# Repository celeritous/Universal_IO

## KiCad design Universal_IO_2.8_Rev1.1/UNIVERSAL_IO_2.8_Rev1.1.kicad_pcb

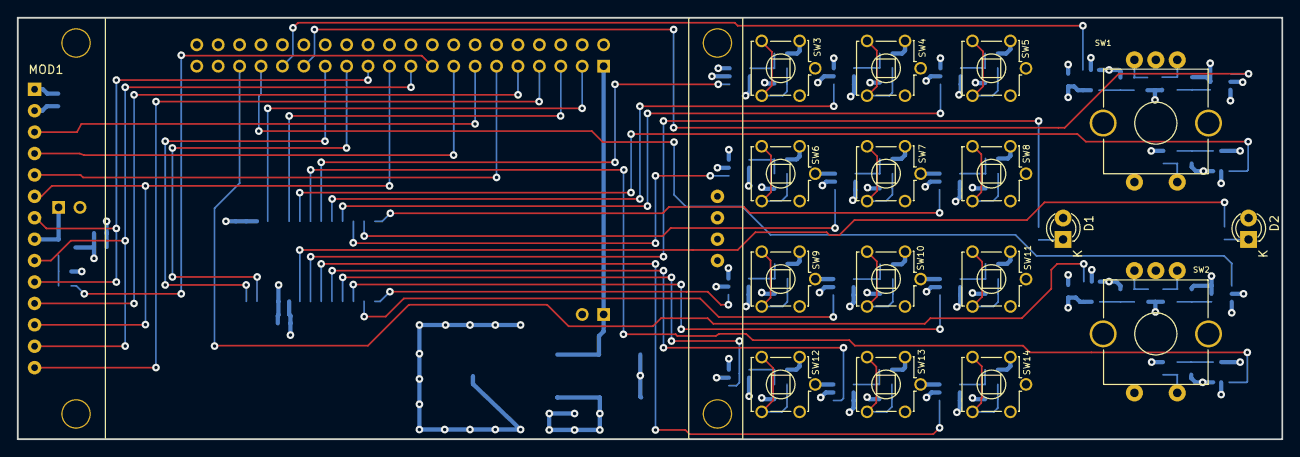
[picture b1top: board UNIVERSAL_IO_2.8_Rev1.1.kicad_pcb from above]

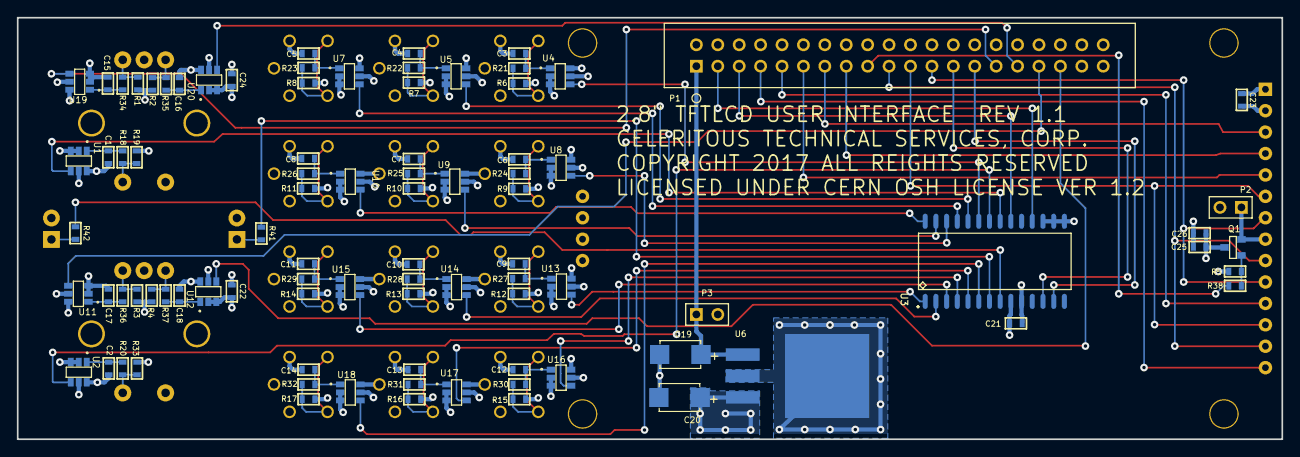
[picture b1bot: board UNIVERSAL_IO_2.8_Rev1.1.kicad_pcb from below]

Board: 4 copper layers, 150.0 x 50.0 mm, 107 parts (90 on the bottom side), 76 nets.

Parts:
C1, C2, C3, C4, C5, C6, C7, C8, C9, C10, C11, C12, C13, C14, C15, C16, C17, C18, C21, C22, C23, C24, C25: 0.10uF; P0603
C19, C20: 47uF; CAPACITOR_TANTALUM_C
C26: 10.0uF; P0603
D1, D2: Led_Small; LED_3MM_TH
MOD1: TFT_320X240_2.4_SPI; TFT_320x260_2.8_SPI
P1: Header_2x20; Header_2x20_Shrouded_100mil
P2, P3: Header_2x1; Header_2x1_Shrouded_100mil
Q1: CMPDM302PH; SOT23-3
R1, R2, R3, R4, R5, R6, R7, R8, R9, R10, R11, R12, R13, R14, R15, R16, R17, R19, R33: 10.0kΩ; P0603
R18, R20, R21, R22, R23, R24, R25, R26, R27, R28, R29, R30, R31, R32, R34, R35, R36, R37: 1.00kΩ; P0603
R38, R41, R42: 470.0Ω; P0603
SW1, SW2: ENCODER_W/PB; SW_PEC11_QUAD_ENCODER_TH_PB
SW3, SW4, SW5, SW6, SW7, SW8, SW9, SW10, SW11, SW12, SW13, SW14: PUSHBUTTON_SPST_6MM_TH_GND; SWITCH_PB_6MM_TH_GND
U1, U2, U4, U5, U7, U8, U9, U10, U11, U12, U13, U14, U15, U16, U17, U18, U19, U20: SN74LVC1G97; SOT23-6
U3: MCP23017; SOIC127P1034X267-28
U6: MCP1826S-3302; TO263-3

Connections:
+3.3V: C20.1, C21.1, C22.1, C23.1, C24.1, C25.1, C26.1, D1.A, D2.A, MOD1.1, P2.2, P3.2, Q1.2, R1.1, R2.1, R3.1, R4.1, R5.2, R6.1, R7.1, R8.1, R9.1, R10.1, R11.1, R12.1, R13.1, R14.1, R15.1, R16.1, R17.1, R19.2, R33.2, U1.5, U2.5, U3.9, U4.5, U5.5, U6.3, U7.5, U8.5, U9.5, U10.5, U11.5, U12.5, U13.5, U14.5, U15.5, U16.5, U17.5, U18.5, U19.5, U20.5
+4.3V: C19.1, P1.1, P3.1, U6.1
/DB1: U1.4, U3.21
/DB2: U2.4, U3.22
/DB3: U3.23, U4.4
/DB4: U3.24, U5.4
/DB5: U3.25, U7.4
/DB6: U3.26, U8.4
/DB7: U3.27, U9.4
/DB8: U3.28, U10.4
/DB9: U3.1, U13.4
/DB10: U3.2, U14.4
/DB11: U3.3, U15.4
/DB12: U3.4, U16.4
/DB13: U3.5, U17.4
/DB14: U3.6, U18.4
/DISP_CD: MOD1.5, P1.11
/DISP_CS: MOD1.3, P1.13
/DISP_LED: MOD1.8, P2.1, Q1.3
/DISP_PENIRQ: MOD1.14, P1.7
/DISP_RST: MOD1.4, P1.15
/DISP_TCS: MOD1.11, P1.9
/ENCODER_1A: P1.29, U19.4
/ENCODER_1B: P1.31, U20.4
/ENCODER_2A: P1.33, U11.4
/ENCODER_2B: P1.35, U12.4
/EXP_INT: P1.5, U3.20
/EXP_RST: P1.3, U3.18
/I2C_SCL: P1.25, U3.12
/I2C_SDA: P1.27, U3.13
/LED1: R41.1, U3.7
/LED2: R42.1, U3.8
/PB1: C1.1, R18.2, U1.1
/PB2: C2.1, R20.2, U2.1
/PB3: C3.1, R21.2, U4.1
/PB4: C4.1, R22.2, U5.1
/PB5: C5.1, R23.2, U7.1
/PB6: C6.1, R24.2, U8.1
/PB7: C7.1, R25.2, U9.1
/PB8: C8.1, R26.2, U10.1
/PB9: C9.1, R27.2, U13.1
/PB10: C10.1, R28.2, U14.1
/PB11: C11.1, R29.2, U15.1
/PB12: C12.1, R30.2, U16.1
/PB13: C13.1, R31.2, U17.1
/PB14: C14.1, R32.2, U18.1
/PHA1: R1.2, R34.1, SW1.1
/PHA1D: C15.1, R34.2, U19.1
/PHA2: R3.2, R36.1, SW2.1
/PHA2D: C17.1, R36.2, U11.1
/PHB1: R2.2, R35.1, SW1.3
/PHB1D: C16.1, R35.2, U20.1
/PHB2: R4.2, R37.1, SW2.3
/PHB2D: C18.1, R37.2, U12.1
/PWM: P1.17, R38.1
/SPI_MISO: MOD1.9, MOD1.13, P1.19
/SPI_MOSI: MOD1.6, MOD1.12, P1.21
/SPI_SCK: MOD1.7, MOD1.10, P1.23
/SW3: R6.2, R21.1, SW3.1, SW3.2
/SW4: R7.2, R22.1, SW4.1, SW4.2
/SW5: R8.2, R23.1, SW5.1, SW5.2
/SW6: R9.2, R24.1, SW6.1, SW6.2
/SW7: R10.2, R25.1, SW7.1, SW7.2
/SW8: R11.2, R26.1, SW8.1, SW8.2
/SW9: R12.2, R27.1, SW9.1, SW9.2
/SW10: R13.2, R28.1, SW10.1, SW10.2
/SW11: R14.2, R29.1, SW11.1, SW11.2
/SW12: R15.2, R30.1, SW12.1, SW12.2
/SW13: R16.2, R31.1, SW13.1, SW13.2
/SW14: R17.2, R32.1, SW14.1, SW14.2
GND: C1.2, C2.2, C3.2, C4.2, C5.2, C6.2, C7.2, C8.2, C9.2, C10.2, C11.2, C12.2, C13.2, C14.2, C15.2, C16.2, C17.2, C18.2, C19.2, C20.2, C21.2, C22.2, C23.2, C24.2, C25.2, C26.2, MOD1.2, P1.2, P1.4, P1.6, P1.8, P1.10, P1.12, P1.14, P1.16, P1.18, P1.20, P1.22, P1.24, P1.26, P1.28, P1.30, P1.32, P1.34, P1.36, P1.38, P1.40, SW1.2, SW1.4, SW2.2, SW2.4, SW3.3, SW3.4, SW3.5, SW4.3, SW4.4, SW4.5, SW5.3, SW5.4, SW5.5, SW6.3, SW6.4, SW6.5, SW7.3, SW7.4, SW7.5, SW8.3, SW8.4, SW8.5, SW9.3, SW9.4, SW9.5, SW10.3, SW10.4, SW10.5, SW11.3, SW11.4, SW11.5, SW12.3, SW12.4, SW12.5, SW13.3, SW13.4, SW13.5, SW14.3, SW14.4, SW14.5, U1.2, U1.3, U1.6, U2.2, U2.3, U2.6, U3.10, U3.15, U3.16, U3.17, U4.2, U4.3, U4.6, U5.2, U5.3, U5.6, U6.2, U6.4, U7.2, U7.3, U7.6, U8.2, U8.3, U8.6, U9.2, U9.3, U9.6, U10.2, U10.3, U10.6, U11.2, U11.3, U11.6, U12.2, U12.3, U12.6, U13.2, U13.3, U13.6, U14.2, U14.3, U14.6, U15.2, U15.3, U15.6, U16.2, U16.3, U16.6, U17.2, U17.3, U17.6, U18.2, U18.3, U18.6, U19.2, U19.3, U19.6, U20.2, U20.3, U20.6
unnamed: D1.K, R41.2
unnamed: D2.K, R42.2
unnamed: Q1.1, R5.1, R38.2
unnamed: R18.1, R19.1, SW1.5
unnamed: R20.1, R33.1, SW2.5

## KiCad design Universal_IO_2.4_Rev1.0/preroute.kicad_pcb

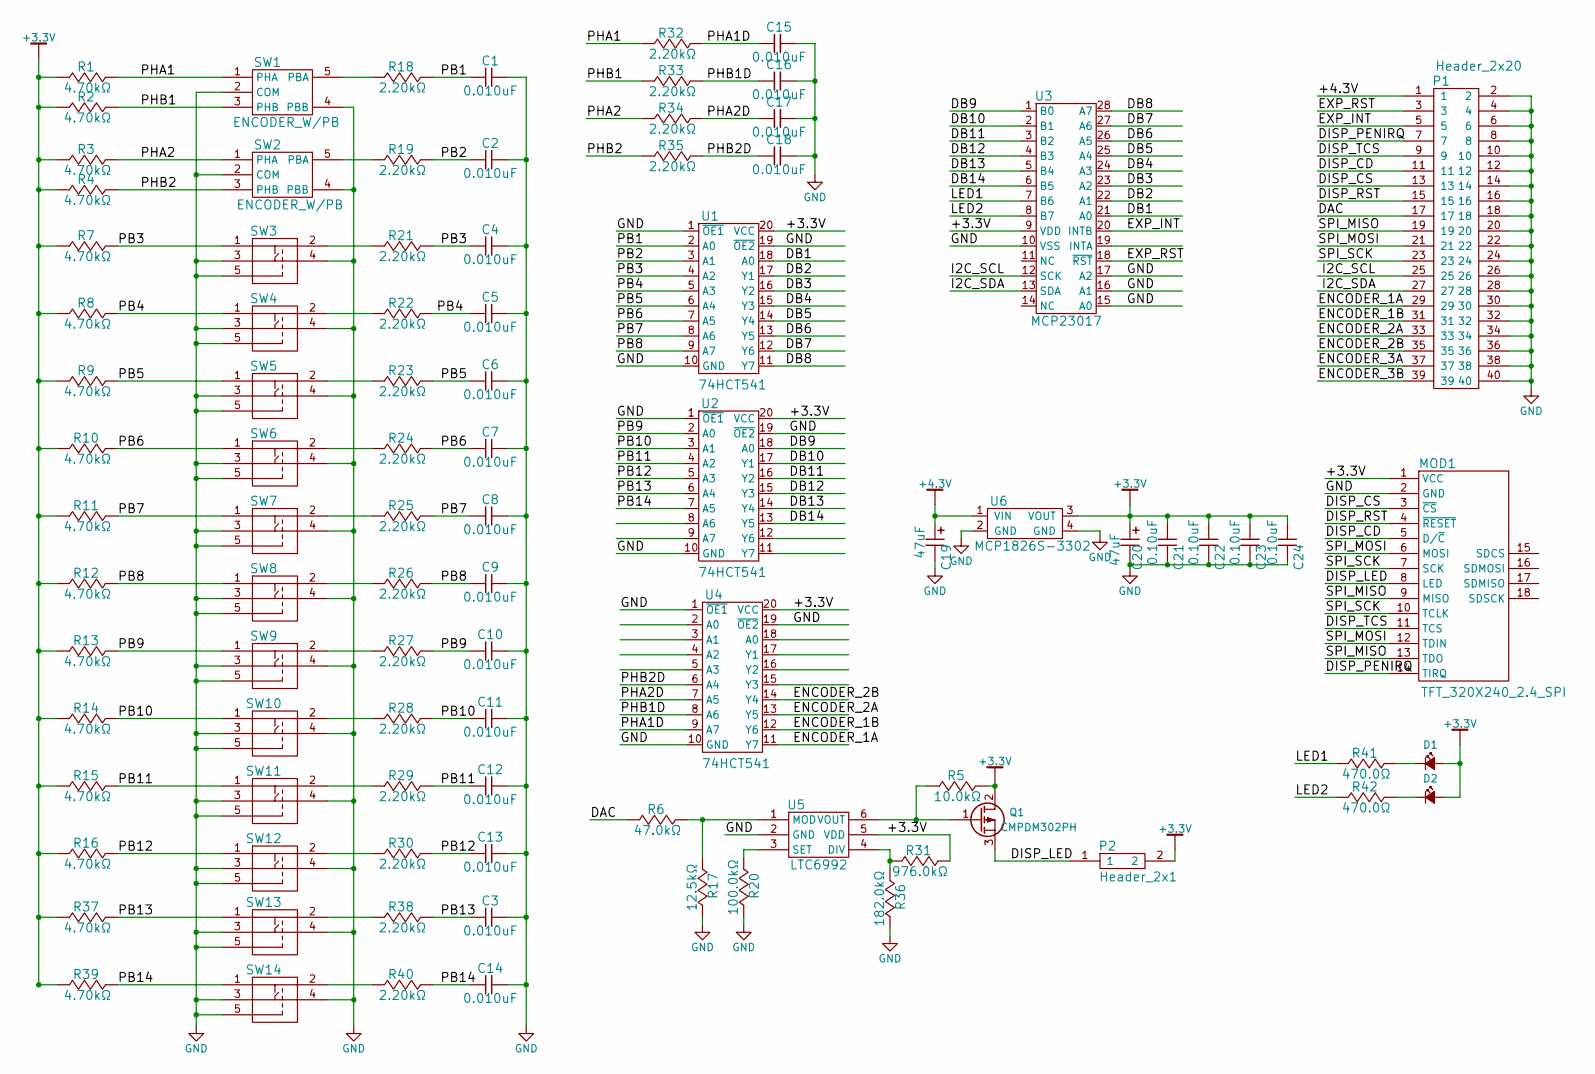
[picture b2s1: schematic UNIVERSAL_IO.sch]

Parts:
C1, C2, C3, C4, C5, C6, C7, C8, C9, C10, C11, C12, C13, C14, C15, C16, C17, C18: 0.010uF; P0805
C19, C20: 47uF; CAPACITOR_TANTALUM_C
C21, C22, C23, C24: 0.10uF; P0603
D1, D2: Led_Small; LED_3MM_TH
MOD1: TFT_320X240_2.4_SPI; TFT_320x260_2.8_SPI
P1: Header_2x20; Header_2x20_Shrouded_100mil
P2: Header_2x1; Header_2x1_Shrouded_100mil
Q1: CMPDM302PH; SOT23-3
R1, R2, R3, R4, R7, R8, R9, R10, R11, R12, R13, R14, R15, R16, R37, R39: 4.70kΩ; P0805
R5: 10.0kΩ; P0805
R6: 47.0kΩ; P0805
R17: 12.5kΩ; P0805
R18, R19, R21, R22, R23, R24, R25, R26, R27, R28, R29, R30, R32, R33, R34, R35, R38, R40: 2.20kΩ; P0805
R20: 100.0kΩ; P0805
R31: 976.0kΩ; P0805
R36: 182.0kΩ; P0805
R41, R42: 470.0Ω; P0805
SW1, SW2: ENCODER_W/PB; SW_PEC11_QUAD_ENCODER_TH_PB
SW3, SW4, SW5, SW6, SW7, SW8, SW9, SW10, SW11, SW12, SW13, SW14: PUSHBUTTON_SPST_6MM_TH_GND; SWITCH_PB_6MM_TH_GND
U1, U2, U4: 74HCT541; SOIC127P1032X265-20
U3: MCP23017; SOIC127P1034X267-28
U5: LTC6992; SOT23-6
U6: MCP1826S-3302; TO263-3

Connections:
+3.3V: C20.1, C21.1, C22.1, C23.1, C24.1, D1.A, D2.A, MOD1.1 (VCC), P2.2, Q1.2 (D), R1.1, R2.1, R3.1, R4.1, R5.2, R7.1, R8.1, R9.1, R10.1, R11.1, R12.1, R13.1, R14.1, R15.1, R16.1, R31.2, R37.1, R39.1, U1.20 (VCC), U2.20 (VCC), U3.9 (VDD), U4.20 (VCC), U5.5 (VDD), U6.3 (VOUT)
+4.3V: C19.1, P1.1, U6.1 (VIN)
/DAC: P1.17, R6.1
/DB1: U1.18 (A0), U3.21 (A0)
/DB2: U1.17 (Y1), U3.22 (A1)
/DB3: U1.16 (Y2), U3.23 (A2)
/DB4: U1.15 (Y3), U3.24 (A3)
/DB5: U1.14 (Y4), U3.25 (A4)
/DB6: U1.13 (Y5), U3.26 (A5)
/DB7: U1.12 (Y6), U3.27 (A6)
/DB8: U1.11 (Y7), U3.28 (A7)
/DB9: U2.18 (A0), U3.1 (B0)
/DB10: U2.17 (Y1), U3.2 (B1)
/DB11: U2.16 (Y2), U3.3 (B2)
/DB12: U2.15 (Y3), U3.4 (B3)
/DB13: U2.14 (Y4), U3.5 (B4)
/DB14: U2.13 (Y5), U3.6 (B5)
/DISP_CD: MOD1.5 (D/~C), P1.11
/DISP_CS: MOD1.3 (~CS), P1.13
/DISP_LED: MOD1.8 (LED), P2.1, Q1.3 (S)
/DISP_PENIRQ: MOD1.14 (TIRQ), P1.7
/DISP_RST: MOD1.4 (~RESET), P1.15
/DISP_TCS: MOD1.11 (TCS), P1.9
/ENCODER_1A: P1.29, U4.11 (Y7)
/ENCODER_1B: P1.31, U4.12 (Y6)
/ENCODER_2A: P1.33, U4.13 (Y5)
/ENCODER_2B: P1.35, U4.14 (Y4)
/EXP_INT: P1.5, U3.20 (INTB)
/EXP_RST: P1.3, U3.18 (~RST)
/LED1: R41.1, U3.7 (B6)
/LED2: R42.1, U3.8 (B7)
/PB1: C1.1, R18.2, U1.2 (A0)
/PB2: C2.1, R19.2, U1.3 (A1)
/PB3: C4.1, R7.2, R21.2, SW3.1, U1.4 (A2)
/PB4: C5.1, R8.2, R22.2, SW4.1, U1.5 (A3)
/PB5: C6.1, R9.2, R23.2, SW5.1, U1.6 (A4)
/PB6: C7.1, R10.2, R24.2, SW6.1, U1.7 (A5)
/PB7: C8.1, R11.2, R25.2, SW7.1, U1.8 (A6)
/PB8: C9.1, R12.2, R26.2, SW8.1, U1.9 (A7)
/PB9: C10.1, R13.2, R27.2, SW9.1, U2.2 (A0)
/PB10: C11.1, R14.2, R28.2, SW10.1, U2.3 (A1)
/PB11: C12.1, R15.2, R29.2, SW11.1, U2.4 (A2)
/PB12: C13.1, R16.2, R30.2, SW12.1, U2.5 (A3)
/PB13: C3.1, R37.2, R38.2, SW13.1, U2.6 (A4)
/PB14: C14.1, R39.2, R40.2, SW14.1, U2.7 (A5)
/PHA1: R1.2, R32.1, SW1.1 (PHA)
/PHA1D: C15.1, R32.2, U4.9 (A7)
/PHA2: R3.2, R34.1, SW2.1 (PHA)
/PHA2D: C17.1, R34.2, U4.7 (A5)
/PHB1: R2.2, R33.1, SW1.3 (PHB)
/PHB1D: C16.1, R33.2, U4.8 (A6)
/PHB2: R4.2, R35.1, SW2.3 (PHB)
/PHB2D: C18.1, R35.2, U4.6 (A4)
/SPI_MISO: MOD1.9 (MISO), MOD1.13 (TDO), P1.19
/SPI_MOSI: MOD1.6 (MOSI), MOD1.12 (TDIN), P1.21
/SPI_SCK: MOD1.7 (SCK), MOD1.10 (TCLK), P1.23
GND: C1.2, C2.2, C3.2, C4.2, C5.2, C6.2, C7.2, C8.2, C9.2, C10.2, C11.2, C12.2, C13.2, C14.2, C15.2, C16.2, C17.2, C18.2, C19.2, C20.2, C21.2, C22.2, C23.2, C24.2, MOD1.2 (GND), P1.2, P1.4, P1.6, P1.8, P1.10, P1.12, P1.14, P1.16, P1.18, P1.20, P1.22, P1.24, P1.26, P1.28, P1.30, P1.32, P1.34, P1.36, P1.38, P1.40, R17.2, R20.2, R36.2, SW1.2 (COM), SW1.4 (PBB), SW2.2 (COM), SW2.4 (PBB), SW3.3, SW3.4, SW3.5 (GND), SW4.3, SW4.4, SW4.5 (GND), SW5.3, SW5.4, SW5.5 (GND), SW6.3, SW6.4, SW6.5 (GND), SW7.3, SW7.4, SW7.5 (GND), SW8.3, SW8.4, SW8.5 (GND), SW9.3, SW9.4, SW9.5 (GND), SW10.3, SW10.4, SW10.5 (GND), SW11.3, SW11.4, SW11.5 (GND), SW12.3, SW12.4, SW12.5 (GND), SW13.3, SW13.4, SW13.5 (GND), SW14.3, SW14.4, SW14.5 (GND), U1.1 (~OE1), U1.10 (GND), U1.19 (~OE2), U2.1 (~OE1), U2.10 (GND), U2.19 (~OE2), U3.10 (VSS), U3.15 (A0), U3.16 (A1), U3.17 (A2), U4.1 (~OE1), U4.10 (GND), U4.19 (~OE2), U5.2 (GND), U6.2 (GND), U6.4 (GND)
unnamed: D1.K, R41.2
unnamed: D2.K, R42.2
unnamed: Q1.1 (G), R5.1, U5.6 (VOUT)
unnamed: R6.2, R17.1, U5.1 (MOD)
unnamed: R18.1, SW1.5 (PBA)
unnamed: R19.1, SW2.5 (PBA)
unnamed: R20.1, U5.3 (SET)
unnamed: R21.1, SW3.2
unnamed: R22.1, SW4.2
unnamed: R23.1, SW5.2
unnamed: R24.1, SW6.2
unnamed: R25.1, SW7.2
unnamed: R26.1, SW8.2
unnamed: R27.1, SW9.2
unnamed: R28.1, SW10.2
unnamed: R29.1, SW11.2
unnamed: R30.1, SW12.2
unnamed: R31.1, R36.1, U5.4 (DIV)
unnamed: R38.1, SW13.2
unnamed: R40.1, SW14.2

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
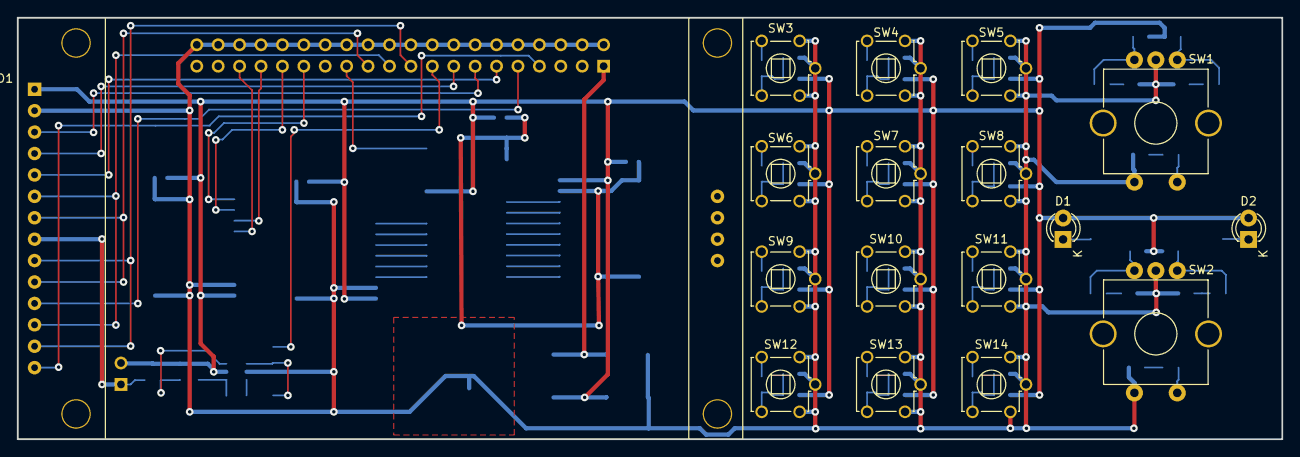
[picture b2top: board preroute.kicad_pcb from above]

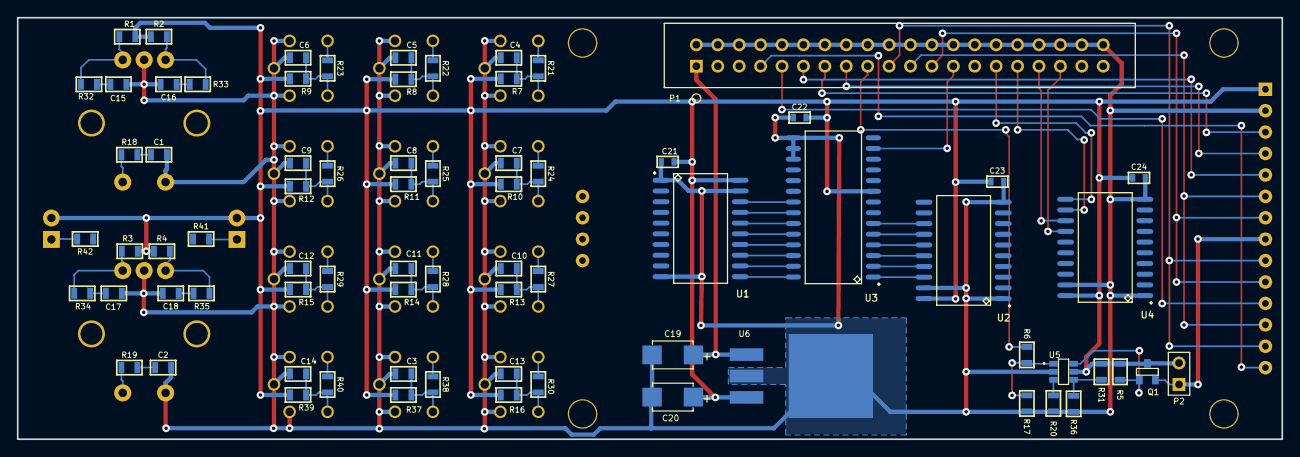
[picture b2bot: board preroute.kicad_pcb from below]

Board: 2 copper layers, 150.0 x 50.0 mm, 92 parts (75 on the bottom side), 78 nets.

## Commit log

2018-06-29 Update Repository to Rev 1.1 & correct size to 2.8"
2018-07-05 Update 7/1/2018

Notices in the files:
Universal_IO_2.8_Rev1.1/UNIVERSAL_IO_2.8_Rev1.1.kicad_pcb:
COPYRIGHT 2017 ALL REIGHTS RESERVED
LICENSED UNDER CERN OSH LICENSE VER 1.2
